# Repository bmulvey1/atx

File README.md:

atx

simple breakout board for an atx power supply - provides +-12v, 5vsb, 5v, 3.3v with indicator LEDs and a switch for PS_ON

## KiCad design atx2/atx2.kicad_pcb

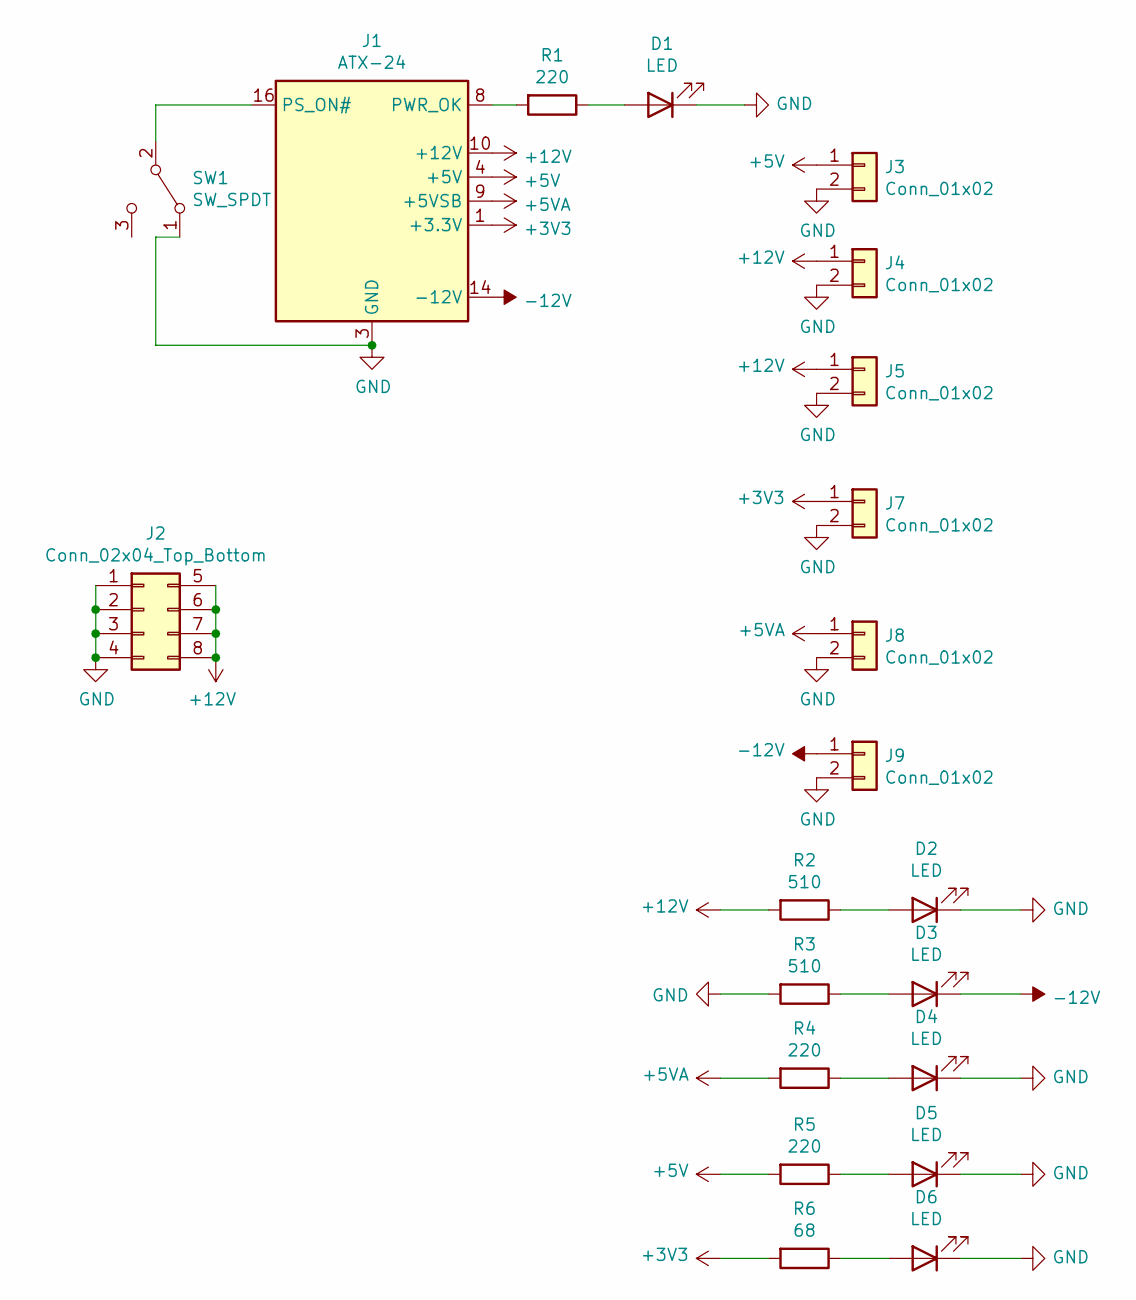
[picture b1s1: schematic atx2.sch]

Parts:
D1, D2, D3, D4, D5, D6: LED; LED_1206_3216Metric
J1: ATX-24; Molex_Mini-Fit_Jr_5566-24A2_2x12_P4.20mm_Vertical
J2: Conn_02x04_Top_Bottom; Molex_Mini-Fit_Jr_5566-08A2_2x04_P4.20mm_Vertical
J3, J4, J5, J7, J8, J9: Conn_01x02; TerminalBlock_Wuerth_691311400102_P7.62mm
R1, R4, R5: 220; R_1206_3216Metric
R2, R3: 510; R_1206_3216Metric
R6: 68; R_1206_3216Metric
SW1: SW_SPDT; SW_E-Switch_EG1271_DPDT

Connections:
+3V3: J1.1 (+3.3V), J1.2 (+3.3V), J1.12 (+3.3V), J1.13 (+3.3V), J7.1, R6.2
+5V: J1.4 (+5V), J1.6 (+5V), J1.21 (+5V), J1.22 (+5V), J1.23 (+5V), J3.1, R5.2
+5VA: J1.9 (+5VSB), J8.1, R4.2
+12V: J1.10 (+12V), J1.11 (+12V), J2.5, J2.6, J2.7, J2.8, J4.1, J5.1, R2.2
-12V: D3.1 (K), J1.14 (-12V), J9.1
GND: D1.1 (K), D2.1 (K), D4.1 (K), D5.1 (K), D6.1 (K), J1.3 (GND), J1.5 (GND), J1.7 (GND), J1.15 (GND), J1.17 (GND), J1.18 (GND), J1.19 (GND), J1.24 (GND), J2.1, J2.2, J2.3, J2.4, J3.2, J4.2, J5.2, J7.2, J8.2, J9.2, R3.2, SW1.1 (A)
unnamed: D1.2 (A), R1.1
unnamed: D2.2 (A), R2.1
unnamed: D3.2 (A), R3.1
unnamed: D4.2 (A), R4.1
unnamed: D5.2 (A), R5.1
unnamed: D6.2 (A), R6.1
unnamed: J1.8 (PWR_OK), R1.2
unnamed: J1.16 (PS_ON#), SW1.2 (B)

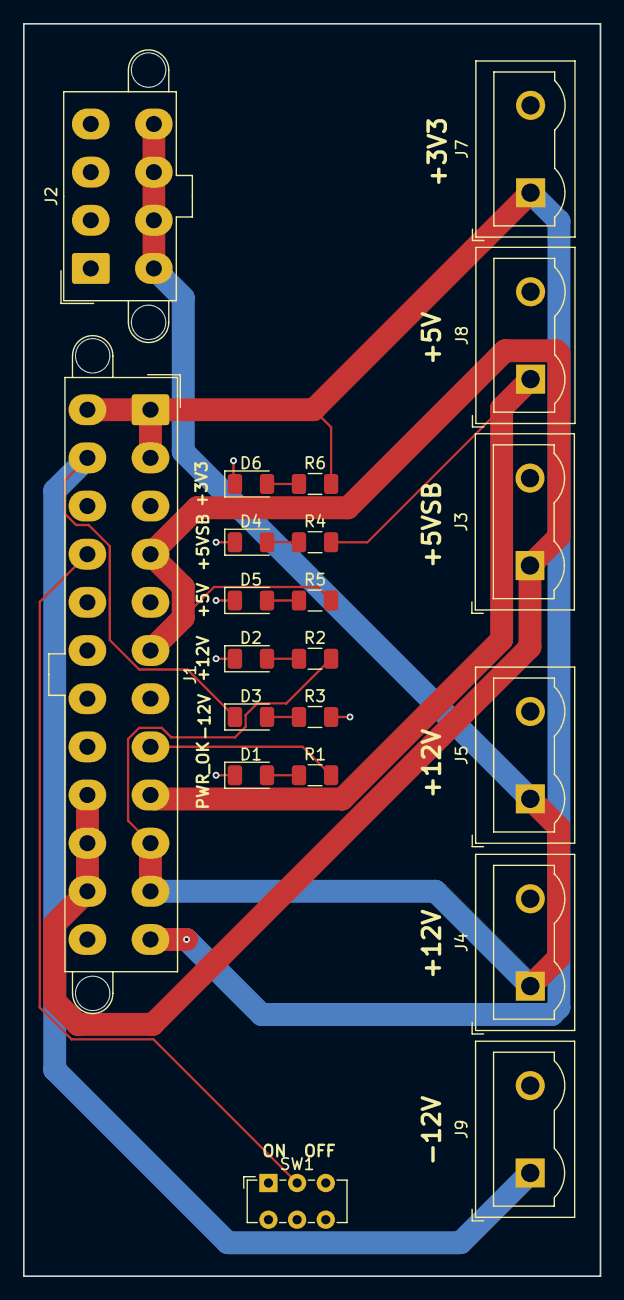
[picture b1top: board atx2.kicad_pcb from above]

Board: 2 copper layers, 50.3 x 109.2 mm, 21 parts (0 on the bottom side), 14 nets.

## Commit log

2020-12-17 partial design
2021-01-08 design-v1
